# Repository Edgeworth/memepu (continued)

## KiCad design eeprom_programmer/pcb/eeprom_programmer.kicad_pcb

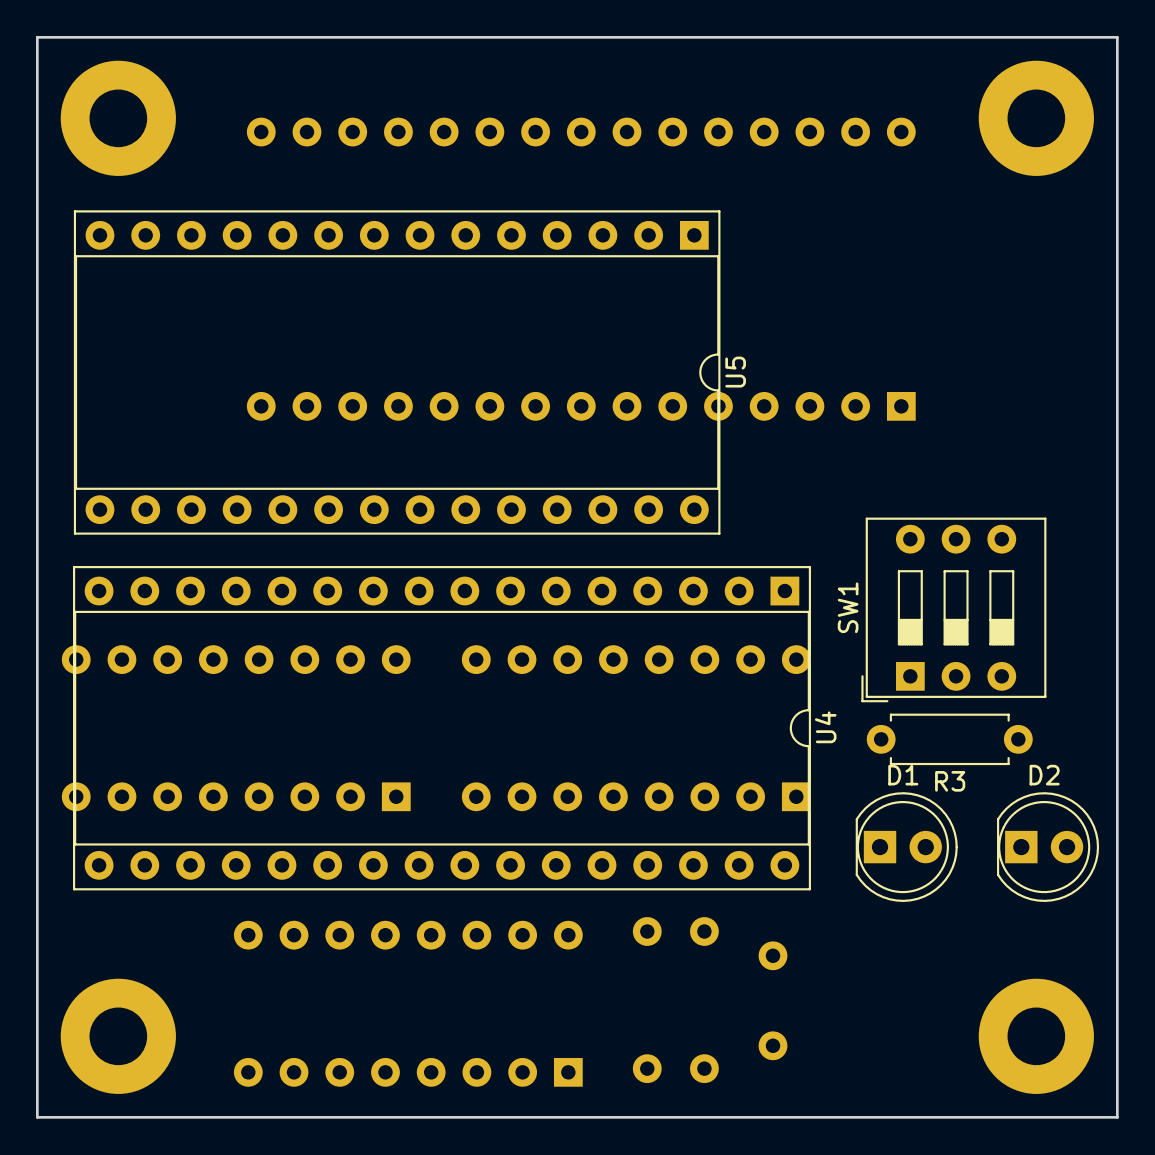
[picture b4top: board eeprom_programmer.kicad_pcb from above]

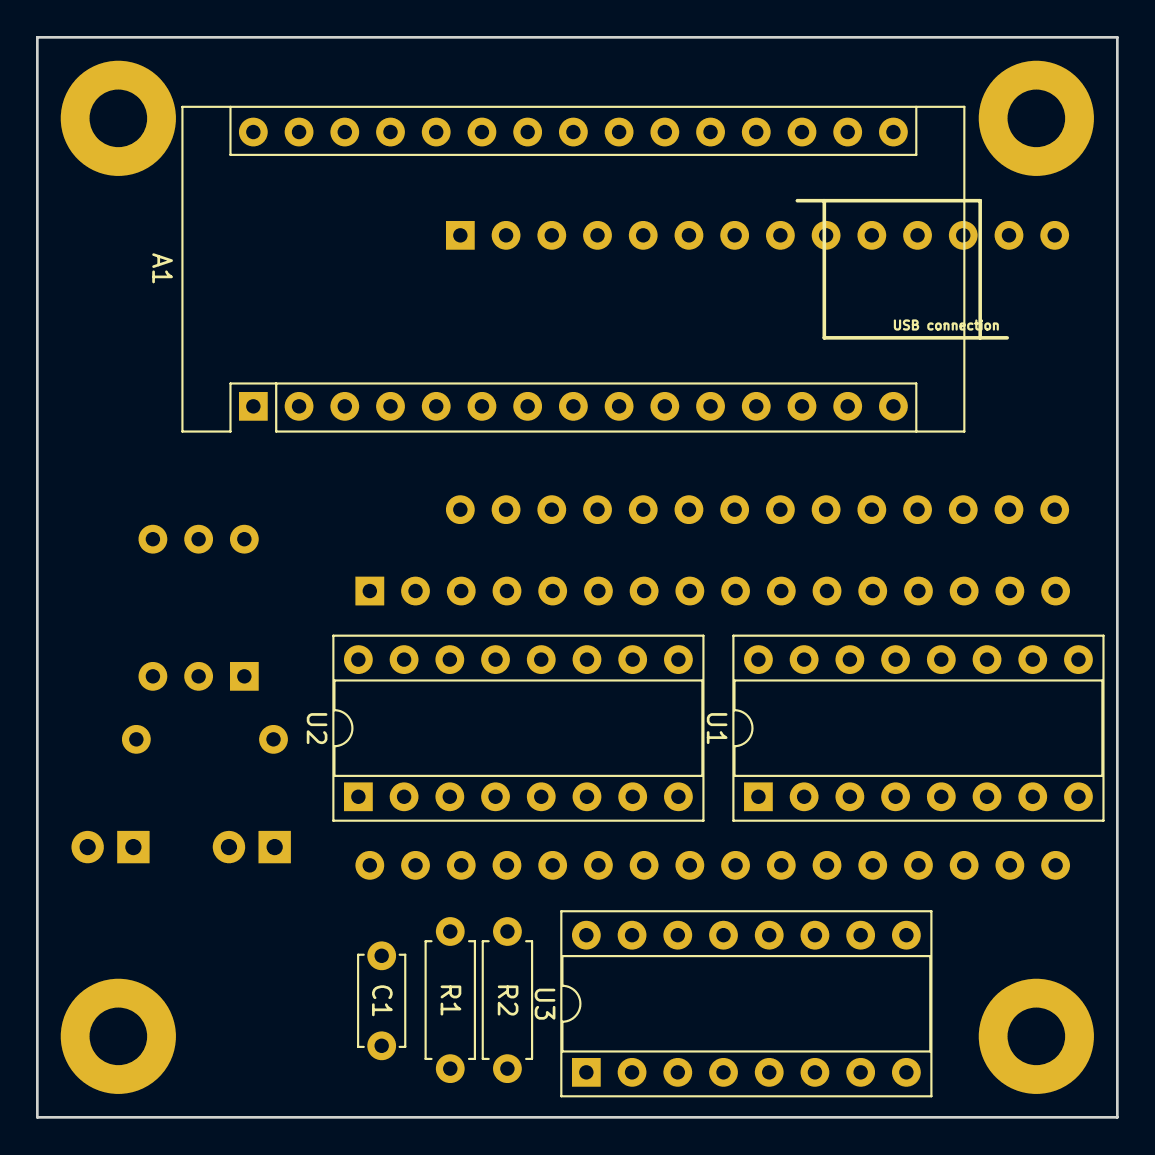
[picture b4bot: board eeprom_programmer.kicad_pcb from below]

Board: 2 copper layers, 60.0 x 60.0 mm, 17 parts (7 on the bottom side), 43 nets, no tracks yet.

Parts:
A1: Arduino_Nano_v3.x; Arduino_Nano
C1: 0.1uF; C_Disc_D5.0mm_W2.5mm_P5.00mm
D1, D2: LED; LED_D5.0mm
M1, M2, M3, M4: MountingHole_3.2mm_M3_Pad
R1, R2: 1K; R_Axial_DIN0207_L6.3mm_D2.5mm_P7.62mm_Horizontal
R3: 100K; R_Axial_DIN0207_L6.3mm_D2.5mm_P7.62mm_Horizontal
SW1: SW_DIP_x03; SW_DIP_SPSTx03_Slide_9.78x9.8mm_W7.62mm_P2.54mm
U1, U2, U3: 74HC595; DIP-16_W7.62mm_Socket
U4: SST39SF040; DIP-32_W15.24mm_Socket
U5: AT28C64B; DIP-28_W15.24mm_Socket

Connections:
+5V: A1.27, C1.1, SW1.6, U1.10, U1.16, U2.10, U2.16, U3.10, U3.16, U4.32, U5.28
/A0: U1.15, U4.12, U5.10
/A1: U1.1, U4.11, U5.9
/A2: U1.2, U4.10, U5.8
/A3: U1.3, U4.9, U5.7
/A4: U1.4, U4.8, U5.6
/A5: U1.5, U4.7, U5.5
/A6: U1.6, U4.6, U5.4
/A7: U1.7, U4.5, U5.3
/A8: U2.15, U4.27, U5.25
/A9: U2.1, U4.26, U5.24
/A10: U2.2, U4.23, U5.21
/A11: U2.3, U4.25, U5.23
/A12: U2.4, U4.4, U5.2
/A13: U2.5, U4.28
/A14: U2.6, U4.29
/A15: U2.7, U4.3
/A16: U3.15, U4.2
/A17: U3.1, U4.30
/A18: U3.2, U4.1
/D0: A1.19, U4.13, U5.11
/D1: A1.20, U4.14, U5.12
/D2: A1.21, U4.15, U5.13
/D3: A1.22, U4.17, U5.15
/D4: A1.23, U4.18, U5.16
/D5: A1.24, U4.19, U5.17
/D6: A1.12, U4.20, U5.18
/D7: A1.13, U4.21, U5.19
/RCLK: A1.7, U1.12, U2.12, U3.12
/SER: A1.5, U1.14
/SRCLK: A1.6, U1.11, U2.11, U3.11
/~OE: A1.9, U4.24, U5.22
/~WE: A1.8, U4.31, U5.27
GND: A1.4, A1.29, C1.2, R1.2, R2.2, R3.1, SW1.4, SW1.5, U1.8, U1.13, U2.8, U2.13, U3.8, U3.13, U4.16, U4.22, U5.14, U5.20
unnamed: A1.10, D1.2
unnamed: A1.11, D2.2
unnamed: A1.14, SW1.3
unnamed: A1.15, SW1.2
unnamed: A1.16, R3.2, SW1.1
unnamed: D1.1, R1.1
unnamed: D2.1, R2.1
unnamed: U1.9, U2.14
unnamed: U2.9, U3.14

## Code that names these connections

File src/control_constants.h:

#ifndef SRC_CONTROL_CONSTANTS_H
#define SRC_CONTROL_CONSTANTS_H

#include "common.h"

// PIN mapping
enum {
  CTRL_IN0 = 0,
  CTRL_IN1 = 1,
  CTRL_IN2 = 2,
  CTRL_IN3 = 3,
  CTRL_IN4 = 4,
  CTRL_OUT0 = 8,
  CTRL_OUT1 = 9,
  CTRL_OUT2 = 10,
  CTRL_OUT3 = 11,
  CTRL_OUT4 = 12,
  CTRL_MULTI0 = 5,
  CTRL_MULTI1 = 6,
  CTRL_MULTI2 = 7,
  CTRL_MULTI3 = 13,
  MLU_SEL0 = 14,
  MLU_SEL1 = 15,
  MLU_SEL2 = 16,
  CTRL_BUS0 = 16,
  CTRL_BUS1 = 17,
  CTRL_BUS2 = 18,
  CTRL_BUS3 = 19,
  CTRL_BUS4 = 20,
  CTRL_BUS5 = 21,
  CTRL_BUS6 = 22,
  CTRL_BUS7 = 23,
};

// IN plane values
enum {
  IN_NONE = 0,
  IN_N_A = 1,
  IN_N_B = 2,
  IN_N_M0 = 3,
  IN_N_M1 = 4,
  IN_N_M2 = 5,
  IN_N_S0 = 6,
  IN_N_S1 = 7,
  IN_N_S2 = 8,
  IN_N_K0 = 9,
  IN_N_K1 = 10,
  IN_N_K2 = 11,
  IN_N_PC0 = 12,
  IN_N_PC1 = 13,
  IN_N_PC2 = 14,
  IN_N_MMU0 = 15,
  IN_N_MMU1 = 16,
  IN_N_MMU2 = 17,
  IN_N_MMU = 18,
  IN_N_MMU_CONTROL = 19,
  IN_N_DISP = 20,
  IN_N_TASK = 21,
  IN_N_OPCODE0 = 22,
  IN_N_OPCODE1 = 23,
  IN_N_INT0 = 24,
  IN_N_INT1 = 25,
  IN_N_INT2 = 26,
  IN_N_INT3 = 27,
  IN_N_INT4 = 28,
  IN_N_INT5 = 29,
  IN_N_INT6 = 30,
  IN_N_INT7 = 31,
};

// OUT plane values
enum {
  OUT_NONE = 0,
  OUT_N_A = 1,
  OUT_N_B = 2,
  OUT_N_M0 = 3,
  OUT_N_M1 = 4,
  OUT_N_M2 = 5,
  OUT_N_S0 = 6,
  OUT_N_S1 = 7,
  OUT_N_S2 = 8,
  OUT_N_K0 = 9,
  OUT_N_K1 = 10,
  OUT_N_K2 = 11,
  OUT_N_PC0 = 12,
  OUT_N_PC1 = 13,
  OUT_N_PC2 = 14,
  OUT_N_STATUS = 15,
  OUT_N_INTERRUPT = 16,
  OUT_N_SUM = 17,
  OUT_N_MMU = 18,
  OUT_N_MMU_CONTROL = 19,
  OUT_N_TASK = 20,
  OUT_N_MLU = 21,
  OUT_N_CTRLLOGIC = 22,
  OUT_N_INT0 = 24,
  OUT_N_INT1 = 25,
  OUT_N_INT2 = 26,
  OUT_N_INT3 = 27,
  OUT_N_INT4 = 28,
  OUT_N_INT5 = 29,
  OUT_N_INT6 = 30,
  OUT_N_INT7 = 31,
};

// MULTI plane values
enum {
  MULTI_NONE = 0,
  MULTI_N_SUB = 1,
  MULTI_N_RESET = 2,
  MULTI_N_RESET_UOP_COUNT = 3,
  MULTI_N_SET_INT_ENABLE = 4,
  MULTI_N_UNSET_INT_ENABLE = 5,
  MULTI_N_PC_INC = 6,
  MULTI_N_OPCODE0_INC = 7,
  MULTI_N_OPCODE1_INC = 8,
  MULTI_N_SP_INC = 9,
  MULTI_N_SP_DEC = 10,
  MULTI_N_KSP_INC = 11,
  MULTI_N_KSP_DEC = 12,
  MULTI_N_ALU_FLAG_SET = 13,
};

// Control logic input address:
enum {
  ADDR_OP0 = 0,
  ADDR_OP1 = 1,
  ADDR_OP2 = 2,
  ADDR_OP3 = 3,
  ADDR_OP4 = 4,
  ADDR_OP5 = 5,
  ADDR_OP6 = 6,
  ADDR_OP7 = 7,
  ADDR_AUX0 = 8, // Corresponds to OP8 to OP11
  ADDR_AUX1 = 9,
  ADDR_AUX2 = 10,
  ADDR_AUX3 = 11,
  ADDR_MICROOP0 = 12,
  ADDR_MICROOP1 = 13,
  ADDR_MICROOP2 = 14,
  ADDR_MICROOP3 = 15,
  ADDR_INT_FLAG = 16,
  ADDR_MMU_FAULT_FLAG = 17,
  ADDR_UNUSED = 18,
};

inline uint32_t in(int in_plane) {
  uint32_t output = 0;
  if (in_plane & 1) output |= 1uL << CTRL_IN0;
  if (in_plane & 2) output |= 1uL << CTRL_IN1;
  if (in_plane & 4) output |= 1uL << CTRL_IN2;
  if (in_plane & 8) output |= 1uL << CTRL_IN3;
  if (in_plane & 16) output |= 1uL << CTRL_IN4;
  return output;
}

inline uint32_t out(int out_plane) {
  uint32_t output = 0;
  if (out_plane & 1) output |= 1uL << CTRL_OUT0;
  if (out_plane & 2) output |= 1uL << CTRL_OUT1;
  if (out_plane & 4) output |= 1uL << CTRL_OUT2;
  if (out_plane & 8) output |= 1uL << CTRL_OUT3;
  if (out_plane & 16) output |= 1uL << CTRL_OUT4;
  return output;
}

inline uint32_t multi(int multi_plane) {
  uint32_t output = 0;
  if (multi_plane & 1) output |= 1uL << CTRL_MULTI0;
  if (multi_plane & 2) output |= 1uL << CTRL_MULTI1;
  if (multi_plane & 4) output |= 1uL << CTRL_MULTI2;
  if (multi_plane & 8) output |= 1uL << CTRL_MULTI3;
  return output;
}

inline uint32_t mlu(int mlu_plane) {
  uint32_t output = 0;
  if (mlu_plane & 1) output |= 1uL << MLU_SEL0;
  if (mlu_plane & 2) output |= 1uL << MLU_SEL1;
  if (mlu_plane & 4) output |= 1uL << MLU_SEL2;
  return output;
}

inline uint32_t bus(int bus_plane) {
  uint32_t output = 0;
  if (bus_plane & 1) output |= 1uL << CTRL_BUS0;
  if (bus_plane & 2) output |= 1uL << CTRL_BUS1;
  if (bus_plane & 4) output |= 1uL << CTRL_BUS2;
  if (bus_plane & 8) output |= 1uL << CTRL_BUS3;
  if (bus_plane & 16) output |= 1uL << CTRL_BUS4;
  if (bus_plane & 32) output |= 1uL << CTRL_BUS5;
  if (bus_plane & 64) output |= 1uL << CTRL_BUS6;
  if (bus_plane & 128) output |= 1uL << CTRL_BUS7;
  return output;
}

inline uint32_t addr_opcode(int opcode) {
  uint32_t output = 0;
  if (opcode & 1) output |= 1uL << ADDR_OP0;
  if (opcode & 2) output |= 1uL << ADDR_OP1;
  if (opcode & 4) output |= 1uL << ADDR_OP2;
  if (opcode & 8) output |= 1uL << ADDR_OP3;
  if (opcode & 16) output |= 1uL << ADDR_OP4;
  if (opcode & 32) output |= 1uL << ADDR_OP5;
  if (opcode & 64) output |= 1uL << ADDR_OP6;
  if (opcode & 128) output |= 1uL << ADDR_OP7;
  return output;
}

inline uint32_t addr_aux(int aux) {
  uint32_t output = 0;
  if (aux & 1) output |= 1uL << ADDR_AUX0;
  if (aux & 2) output |= 1uL << ADDR_AUX1;
  if (aux & 4) output |= 1uL << ADDR_AUX2;
  if (aux & 8) output |= 1uL << ADDR_AUX3;
  return output;
}

inline uint32_t addr_microop(int microop) {
  uint32_t output = 0;
  if (microop & 1) output |= 1uL << ADDR_MICROOP0;
  if (microop & 2) output |= 1uL << ADDR_MICROOP1;
  if (microop & 4) output |= 1uL << ADDR_MICROOP2;
  if (microop & 8) output |= 1uL << ADDR_MICROOP3;
  return output;
}

inline uint32_t addr_int_flag(bool int_flag) {
  return int_flag ? (1uL << ADDR_INT_FLAG) : 0;
}

inline uint32_t addr_mmu_fault_flag(bool mmu_fault_flag) {
  return mmu_fault_flag ? (1uL << ADDR_MMU_FAULT_FLAG) : 0;
}

#endif // SRC_CONTROL_CONSTANTS_H

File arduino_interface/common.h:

#ifndef COMMON_H_
#define COMMON_H_
#include "Arduino.h"

enum {
  BUS0 = 11,
  BUS1 = 10,
  BUS2 = 9,
  BUS3 = 8,
  BUS4 = 7,
  BUS5 = 6,
  BUS6 = 5,
  BUS7 = 4,
  INT_IN_CLK = 3,  // Peripheral (us) should read
  CLK = 2,
  INT_FLAG = A0,  // Flags interrupt to host
  INT_OUT_NCLK = A1  // Peripheral (us) should write to host.
};

const int BUS_PINS[8] = {BUS0, BUS1, BUS2, BUS3, BUS4, BUS5, BUS6, BUS7};

extern char printf_buf[128];
extern int selection;

void printTime(unsigned long us);
void setBusMode(int mode);

#define printf(...) do { \
  snprintf(printf_buf, sizeof(printf_buf), __VA_ARGS__); \
  Serial.print(printf_buf); \
} while (0)

#define PROFILE(x) do { \
  unsigned long st = micros(); \
  x; \
  unsigned long en = micros(); \
  printf("Time for " #x ": "); \
  printTime(en - st); \
  printf("\n"); \
} while(0)

#define CHECK(x) do { \
  if (!(x)) { \
    printf("Assertion " #x " failed."); \
  } \
} while (0)

#endif

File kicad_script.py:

import subprocess

in_labels = [
'~A_IN_NCLK',
'~B_IN_NCLK',
'~M0_IN_NCLK',
'~M1_IN_NCLK',
'~M2_IN_NCLK',
'~S0_IN_NCLK',
'~S1_IN_NCLK',
'~S2_IN_NCLK',
'~K0_IN_NCLK',
'~K1_IN_NCLK',
'~K2_IN_NCLK',
'~PC0_IN_NCLK',
'~PC1_IN_NCLK',
'~PC2_IN_NCLK',
'~MMU0_IN_NCLK',
'~MMU1_IN_NCLK',
'~MMU2_IN_NCLK',
'~MMU_IN_NCLK',
'~MMU_CONTROL_IN_NCLK',
'~DISP_IN_NCLK',
'~TASK_IN_NCLK',
'~OPCODE0_IN_NCLK',
'~OPCODE1_IN_NCLK',
'~INT0_IN_NCLK',
'~INT1_IN_NCLK',
'~INT2_IN_NCLK',
'~INT3_IN_NCLK',
'~INT4_IN_NCLK',
'~INT5_IN_NCLK',
'~INT6_IN_NCLK',
'~INT7_IN_NCLK',
]

# Out of in_labels, when we make CLK versions, these ones should be
# local rather than hierarchical labels.
in_local_labels = ['OPCODE0_IN_NCLK', 'OPCODE1_IN_NCLK']

out_labels = [
'~A_OUT_NCLK',
'~B_OUT_NCLK',
'~M0_OUT_NCLK',
'~M1_OUT_NCLK',
'~M2_OUT_NCLK',
'~S0_OUT_NCLK',
'~S1_OUT_NCLK',
'~S2_OUT_NCLK',
'~K0_OUT_NCLK',
'~K1_OUT_NCLK',
'~K2_OUT_NCLK',
'~PC0_OUT_NCLK',
'~PC1_OUT_NCLK',
'~PC2_OUT_NCLK',
'~STATUS_OUT_NCLK',
'~INTERRUPT_OUT_NCLK',
'~SUM_OUT_NCLK',
'~MMU_OUT_NCLK',
'~MMU_CONTROL_OUT_NCLK',
'~TASK_OUT_NCLK',
'~MLU_OUT_NCLK',
'~CTRLLOGIC_OUT_NCLK',
'~INT0_OUT_NCLK',
'~INT1_OUT_NCLK',
'~INT2_OUT_NCLK',
'~INT3_OUT_NCLK',
'~INT4_OUT_NCLK',
'~INT5_OUT_NCLK',
'~INT6_OUT_NCLK',
'~INT7_OUT_NCLK',
]

ctrl_labels = [
'SUB_NCLK',
'~RESET_NCLK',
'~RESET_UOP_COUNT_NCLK',
'~SET_INT_ENABLE_ASYNC',
'~UNSET_INT_ENABLE_ASYNC',
'PC_INC_NCLK',
'OPCODE0_INC_NCLK', 
'OPCODE1_INC_NCLK',
'~SP_INC_NCLK',
'~SP_DEC_NCLK',
'~KSP_INC_NCLK',
'~KSP_DEC_NCLK',
'ALU_FLAG_SET_NCLK',
]

misc_labels = [
'MICROOP0',
'MICROOP1',
'MICROOP2',
'MICROOP3',
'MMU_READ_FAULT',
'MMU_WRITE_FAULT',
'INT0_LATCH',
'INT1_LATCH',
'INT2_LATCH',
'INT3_LATCH',
'INT4_LATCH',
'INT5_LATCH',
'INT6_LATCH',
'INT7_LATCH',
]

subprocess.call(['xdotool', 'search', '--name', '/Eeschema.*/', 'windowfocus'])

def chunks(l, n):
	return [l[i:i+n] for i in range(0, len(l), n)]

def tr(s):
	m = str.maketrans({'_': 'underscore', '~': 'asciitilde', '.': 'period'})
	return [c.translate(m) for c in s]

def replace(l, fr, to):
	return [i.replace(fr, to) for i in l]

def run_xdotool_key(*keys):
	cmd = ['xdotool', 'key', '--delay', '20'] + list(keys)
	subprocess.call(['echo'] + cmd)
	subprocess.call(cmd)

def nav(s):
	d = {'U': 'Up', 'D': 'Down', 'R': 'Right', 'L': 'Left', 'E': 'Return', 'X': 'Delete', 'T': 'Tab'}
	cur = -1
	mod = ''
	res = []
	for c in s:
		if c.isdigit():
			if cur == -1:
				cur = int(c)
			else:
				cur *= 10
				cur += int(c)
		elif c == 'C':
			mod = 'Control_L+'
		else:
			code = mod+d.get(c, c)
			mod = ''
			if cur != -1:
				code = [code] * cur
				cur = -1
			else:
				code = [code]
			res += code
	return res

def generate_clk_anders(left_labels, right_labels, local_labels=[]):
	col_count = 0
	for l in chunks(list(zip(left_labels, right_labels)), 4):
		run_xdotool_key('l', *tr('CLK'), *nav('ErrEDD'))
		for left, right in l:
			run_xdotool_key('l', *tr(left), *nav('ErrECRR2U'))
			key = 'l' if left in local_labels else 'h'
			run_xdotool_key(key, *tr(right), *nav('ErrE2DCLL2D'))
		run_xdotool_key(*nav('4D'))
		col_count += 1

		if col_count == 2:
			col_count = 0
			run_xdotool_key(*nav('6U4CR2CU2U'))

def generate_nclk_notters(labels):
	for l in chunks(labels, 6):
		for label in l:
			run_xdotool_key('l', *tr(label), *nav('ErrECR2R'))
			run_xdotool_key('l', *tr(label.replace('~', '')), *nav('EE6DCL2L'))
		run_xdotool_key(*nav('6U4CR3CU'))

def import_hierarchical_labels(num):
	for i in range(num):
		run_xdotool_key(*nav('2E2D'))

def shuffle_pins_down(num_pins, num_move):
	for i in range(num_pins):
		run_xdotool_key(*nav('LmDEURmDE' * num_move * 2))
		run_xdotool_key(*nav('2U' + str(num_move * 2) + 'U'))

def shuffle_pins_up(num_pins, num_move):
	for i in range(num_pins):
		run_xdotool_key(*nav('LmUEDRmUE' * num_move * 2))
		run_xdotool_key(*nav('2D' + str(num_move * 2) + 'D'))

def generate_labels(labels, t='l', rot=0):
	for l in labels:
		run_xdotool_key(t, *tr(l), *nav('E' + str(rot) + 'r' + 'EDD'))

def generate_control_logic_leds(labels, diode_labels):
	for l, d in zip(labels, diode_labels):
		run_xdotool_key(*nav('h'), *tr(l), *nav('EECRv'), *tr(d), *nav('ECL4D'))

def change_resistor_values(num):
	for i in range(num):
		run_xdotool_key(*nav('v'), *tr('2.2K'), *nav('E4D'))

def sgn(x):
	return -1 if x < 0 else 1

def x_to_navstr(x):
	big, small = sgn(x) * (abs(x) // 10), sgn(x) * (abs(x) % 10)
	c = ''
	if x < 0: c = 'L'
	if x > 0: c = 'R'
	s = ''
	if big != 0: s += str(abs(big)) + 'C' + c
	if small != 0: s += str(abs(small)) + c
	return s

def pcbnew_rotate_strip_270(num):
	x = 2
	skip = 10
	label = 0
	for i in range(num):
		run_xdotool_key(*nav('EmErrrEm2U%sECD2U%sEm%sDECUE%sE' % (x_to_navstr(x), x_to_navstr(-label), x_to_navstr(label), x_to_navstr(skip))))
		x -= 1
		skip += 1
		label -= 1

def pcbnew_rotate_leds_after(num):
	for i in range(num):
		run_xdotool_key(*nav('EmErrEm5DECR5U'))

pcbnew_rotate_leds_after(8)
# generate_nclk_notters(in_labels)

# in_labels_pos = replace(in_labels, '~', '')
# generate_clk_anders(in_labels_pos, replace(in_labels_pos, 'NCLK', 'CLK'), in_local_labels)

# ctrl_labels_clk_pos = replace(ctrl_labels_clk, '~', '')
# generate_clk_anders(ctrl_labels_clk_pos, replace(ctrl_labels_clk_pos, 'NCLK', 'CLK'), ctrl_local_lables)

# import_hierarchical_labels(len(misc_labels))

# shuffle_pins_down(8, 1)

# generate_labels(test)

# shuffle_pins_up(41, 1)

# labels = replace(ctrl_labels + misc_labels, '_NCLK', '')
# generate_control_logic_leds(labels, replace(labels, '~', ''))

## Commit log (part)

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2019-07-20 Make build faster
2019-07-20 Parser progress.
2019-07-22 Update grammar to make it easier to parse.
2019-07-27 Use clang-format.
2019-08-18 Random progress.
2019-08-23 Mouse input + LW instruction.
2019-08-23 Add speed tracker.
2019-08-23 Fix mnemonics and enable LTO.
2019-08-23 Add ANOT for SB instruction.
2019-08-23 Expand CTRL_DATA to 8 bits.
2019-08-23 Implement SB instruction.
2019-08-23 Add breakpoint functionality to simulator. Still need to add to CLI.
2019-08-23 Add breakpoint support to CLI.
2019-08-24 Process multiple commands for memesim.
2019-08-24 Add RelWithDebInfo options.
2019-08-24 Use ld.gold. run.py in tmp dir. Update MMIO locations. Memesim end on close window.
2019-08-24 Preparing to change to 4 byte word machine.
2019-08-24 Change to 4 byte word machine.
2019-08-25 VGA using 8 bit pixels again.
2019-08-25 Add BNE instruction.
2019-08-25 Add instructions.
2019-08-25 Fix bug
2019-08-27 Add constant calculation and data words to memeasm.
2019-08-27 Display some characters.
2019-08-28 Add chip7474 and interrupt handling.
2019-09-07 Fix run.py script.
2019-09-08 Improve parser.
2019-09-08 Add afl support. Misc fixes.
2019-09-08 Prefix/postfix/unary/precedence expression parsing working.
2019-09-08 Add var token.
2019-09-08 Update memelang a bit.
2019-09-08 Parse function calls and array accesses.
2019-09-08 Implement fn call args.
2019-09-13 Refactor to prepare for multipass parser.
2019-09-14 Small refactor.
2019-09-14 Basic multipass + type stuff done.
2019-09-14 Improve memelang tests.
2019-09-14 Add more tests. Fix bug in expression parser.
2019-09-14 Build using shared libs in debug mode for speed.
2019-09-14 Fix lexer, update tests.
2019-09-14 More tests.
2019-09-14 Fix bug in lexer.
2019-09-15 Add impl parsing.
2019-09-15 Implement ternary expr and if-else.
2019-09-15 Add new test.
2019-09-15 Start interpreter.
2019-09-15 First memelang programme running.
2019-09-15 Add syntax highlighting. Implement more interpreter.
2019-09-15 Interpreter progress.
2019-09-15 Use bug_unless.
2019-09-16 Fix syntax highlighting.
2019-09-24 Readf working.
2019-09-25 Support const vals in array declarations.
2019-09-25 Add while keyword.
2019-09-28 Move builtin types to IDENT. Fix tests.
2019-09-29 Refactor a bit.
2019-09-29 Move Type into maps.
2019-09-30 Progress towards binop interface stuff.
2019-10-04 Fixes.
2019-10-04 First part of a refactor to add memory model simulation to memelang.
2019-10-05 Implement VM.
2019-10-05 Add unsigned int literals.
2019-10-06 Implement explicit conversions.
2019-10-06 Some refactor.
2019-10-07 Working on subtyping.
2019-10-07 Removing var keyword, part 1.
2019-10-08 Remove var keyword. Remove parens from if/match/for/while.
2019-10-08 Update tests.
2019-10-09 Some progress.
2019-10-09 Rename return to ret.
2019-10-13 More understanding of types in parser. Parse type constructors properly.
2019-10-14 Refactoring and more template support.
2019-10-17 Fix some bugs.
2019-10-20 Add stacktrace for VM.
2019-10-20 Fix bug in wildcards.
2019-10-26 Fix bugs.
2019-10-26 Remove auto. Fix parser bug.
2019-10-27 Fix bug with typelists in parser. Fix tests.
2019-10-27 Fuzzing setup
2019-10-27 Fix bugs
2019-10-28 Progress on impls and intfs.
2019-11-02 Run multiple files in memelang.
2019-11-03 Start working on standard library, struct stuff, nad member functions.
2019-11-10 Update iro file.
2019-11-29 Working state.
2019-12-01 Struct static functions.
2019-12-02 Make functions types not varrefs.
2019-12-31 Implement/refactor/improve: - eval() can return types; INVALID_HND vals are types. - autoreset for scopes and nested scopes. - define: - typename: name of something describing a set of types - type: 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
2019-12-31 Deduce wildcards from function args for regular function calls.
2020-01-01 Add CompoundLitFragment
2020-01-01 Reorganise test data.
2020-01-03 Update memelang:
    1. Change type constructors from () to {} (merge with compound literals).
    2. Member functions for structs now must go in an impl block.
    3. Structs use commas instead of semicolons to match enums.
    4. Match syntax updated to: item: { body; }.
    Also impl changes:
    Enums and their variants are now types. Some basic support for type paths.
2020-01-05 Add type context for type deduction. Merge VarRef and UnqualifiedType into Ref. Ref represents an unqualified type/typevalue/value.
2020-01-11 Add concept of FnSetInfo to handle function resolution + deduction.
    Particularly for member access (e.g. templated static function accessed inside
    a struct, need to deduce based on args - or overloaded functions. overloaded
    functions implicitly exist because of multiple implementations).
2020-01-12 Work on structs and misc bugs.
2020-01-12 Fix _malloc.
2020-01-13 Get member functinos working.
2020-01-13 Implement references.
2020-01-20 Add vector, support untyped enums + some other stuff.
2020-01-25 Fix some type issues.
2020-01-25 More progress on type system. Pin googletest to 1.10.
2020-01-25 Update tests (partial).
2020-01-26 Update verilog files for memecad.
2020-01-26 Progress on getting memecad to run on current kpu.
2020-01-26 Fix some references stuff.
2020-01-26 Cleanup.
2020-01-26 Memelang map working.
2020-01-27 Some fixes.
2020-01-27 Update keyboard input program bitmaps.
2020-09-06 Some updates
2020-09-19 vscode
2021-05-01 empty
2021-05-02 Make backtrace not required.
2021-05-02 Rename files.
2021-05-02 Update format.
2021-06-11 Fixes
2021-06-13 Move memeroute to separate project.
2021-06-14 Refactor
2021-06-20 Move some files around.
2021-06-20 Add copyright notice.
2021-06-20 Update clang-format.
2021-06-20 Update header style.
2021-06-20 run dos2unix
2021-06-20 Rename
2021-06-20 Lints
2021-06-20 Move v1 out to a different repo. Lints
2025-09-06 Add py.typed file
2025-11-17 Add comprehensive test coverage for core modules
    Added extensive test suites for:
    - verymeme utility library (file, string, geom, tokenizer, term, bimap, util)
    - memeasm assembler (instructions, labels, branches, immediates, real programs)
    - memesim simulator (KPU operations, commands, state messages, MMIO)
    - memeware microcode (firmware generation, model generation, constants)
    Test coverage includes:
2025-11-17 Add extensive additional test coverage
    Expanded test suites with:
    - ConcurrentQueue tests (11 tests): FIFO order, empty queue, large datasets, structured data
    - CLI and Display tests: Construction and basic functionality
    - Memecad types tests (20 tests): Enums, comparisons, defaults, offset operations
    - Memeasm tests (8 more tests): All registers, max immediates, complex programs, whitespace, branches
    Total additions:
2025-11-17 Add comprehensive integration tests
    Added integration_tests.cpp with 14 test cases covering:
    Cross-module functionality:
    - Microcode → Assembler pipeline (model generation and usage)
    - Assemble/disassemble roundtrip verification
    - Real program assembly from test files
    - Complete firmware generation pipeline
2025-11-18 Fix include order in verymeme_tests.cpp
    Reorder includes to follow codebase conventions:
    1. Standard library headers (alphabetical)
    2. Third-party headers (gtest)
    3. Project headers (alphabetical)
2025-11-18 Fix syntax error in integration_tests.cpp
    Remove space between hex literal and u suffix in EXPECT_EQ
2025-11-18 Fix bugs found during code analysis
    1. bimap.h: Add bounds check in keyForValue()
    - Previously dereferenced iterator without checking validity
    - Now checks iterator != end() before dereferencing
    2. term.h: Fix BG_YELLOW ANSI color code
    - Was incorrectly set to 33 (FG_YELLOW)
    - Now correctly set to 43 (background yellow)
2025-11-19 Remove non-valuable tests
    Removed 35 tests (268 lines) that don't add meaningful value:
    memeware_tests.cpp (14 tests removed):
    - Removed redundant NonEmpty tests (already covered by size tests)
    - Removed trivial constant validation tests (DepthValid)
    - Removed enum distinctness tests (MluEnumValues, ShifterEnumValues)
    - Removed AddressSpace tests that just iterate doing nothing
2025-11-19 Fix broken and incorrect tests
    Critical fixes:
    1. Added missing EXPECT_EQ assertions to 9 tests in memeasm_tests.cpp
    - These tests were computing expected values but never verifying them!
    - Tests were passing without actually testing anything
    - Affected: AddWithImmediate, StoreWord, LoadWord, RelativeBranch,
    BranchNotEqual, ShiftLeft, ShiftRight, AndWithImmediate, NegativeImmediate
